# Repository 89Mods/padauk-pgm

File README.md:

# PMS150 programmer

Open-source programmer for the Padauk PMS150 / PMC150 devices, specifically the SOT23-5 variants (SOIC-8 not supported right now).

This programmer was designed to replicate the scope traces from reverse engineering of the official programmer as closely as possible. The only thing it can’t do is modulate the VDD voltage on the target device, but can change the VPP voltage to any level between 7V and 13V or shut it off entirely.

This project is not yet the simplest possible programmer, just a jumping off point for me to start optimizing from. Its actually quite overkill, as experimenting with the hardware already shows that a constant VPP of 11V is fine and, except for Q3, the FETs could be replaced by direct connections to GPIO pins on the CH32V003. The currents involved are way too tiny to require FETs to switch them. At some point in the future, I will make a new revision of this programmer that is truly as minimal as possible.

Included in this repo is also a primitive Verilog model of this MCU, together with a verilator testbench to help me test my code before I burn it onto a OTP device.

I also added support for PDK13 devices to my fork of the AS Assembler. [Check it out here.](https://github.com/AvalonSemiconductors/asl-avalonsemi/tree/avalonsemi)

The SPI programming interface does not reset properly unless ALL chip pins are floated! I believed that having the SPI lines and GND pin connected to ground while power is reset would be alright, but this breaks things. All must be floated.

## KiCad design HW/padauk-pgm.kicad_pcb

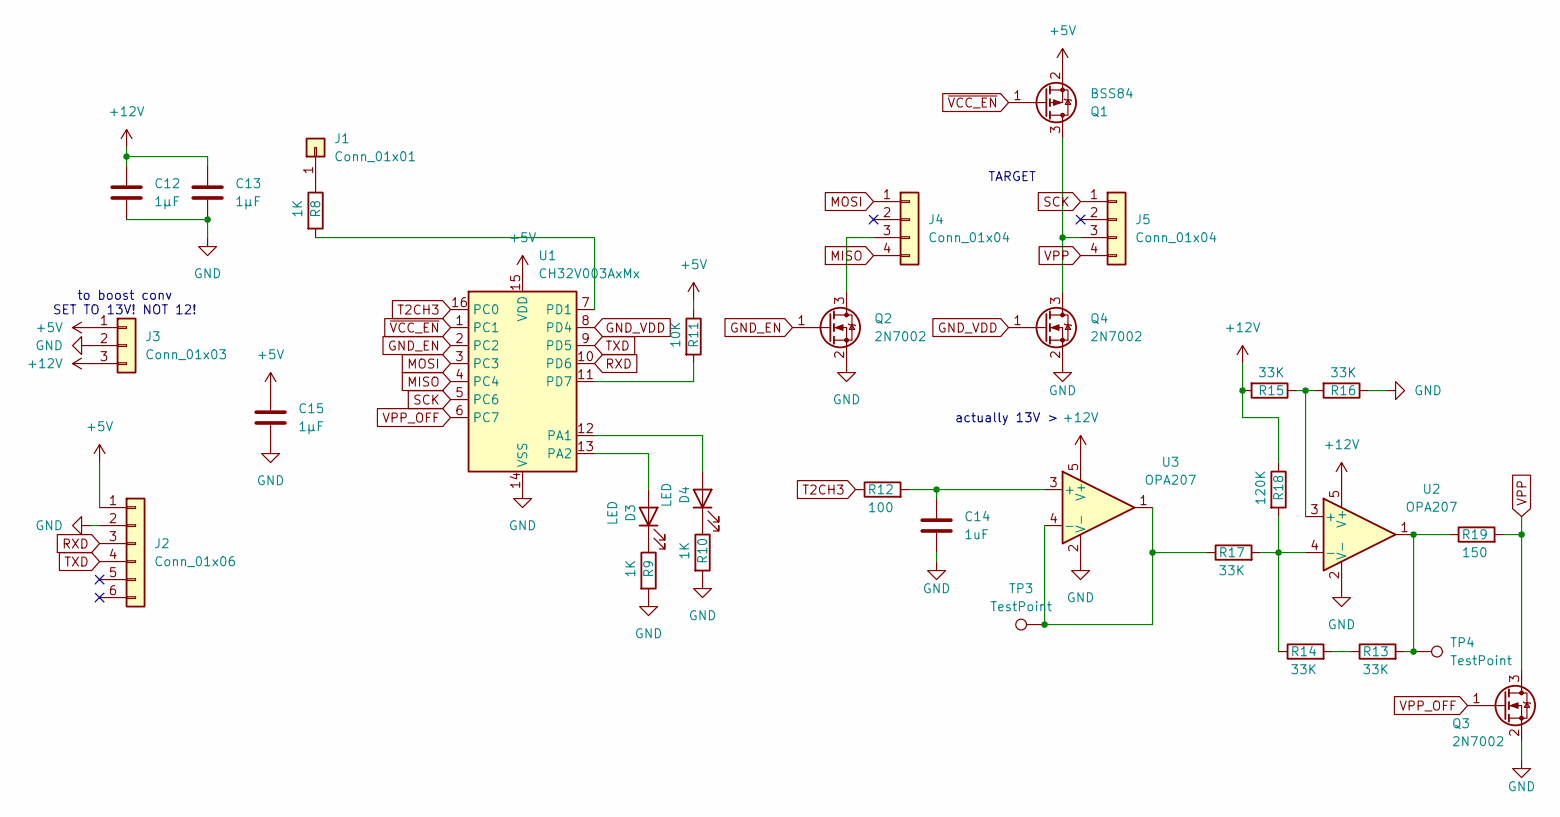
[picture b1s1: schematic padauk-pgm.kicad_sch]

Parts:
C12, C13, C15: 1µF; C_0805_2012Metric_Pad1.18x1.45mm_HandSolder
C14: 1uF; C_1206_3216Metric
D3, D4: LED; LED_1206_3216Metric_Pad1.42x1.75mm_HandSolder
J1: Conn_01x01; PinHeader_1x01_P2.54mm_Vertical
J2: Conn_01x06; PinSocket_1x06_P2.54mm_Vertical
J3: Conn_01x03; PinHeader_1x03_P2.54mm_Vertical
J4, J5: Conn_01x04; PinHeader_1x04_P2.54mm_Vertical
Q1: BSS84; SOT-23
Q2, Q3, Q4: 2N7002; SOT-23
R8, R9, R10: 1K; R_1206_3216Metric_Pad1.30x1.75mm_HandSolder
R11: 10K; R_1206_3216Metric_Pad1.30x1.75mm_HandSolder
R12: 100; R_1206_3216Metric_Pad1.30x1.75mm_HandSolder
R13, R14, R15, R16, R17: 33K; R_1206_3216Metric_Pad1.30x1.75mm_HandSolder
R18: 120K; R_1206_3216Metric_Pad1.30x1.75mm_HandSolder
R19: 150; R_1206_3216Metric_Pad1.30x1.75mm_HandSolder
TP3, TP4: TestPoint; TestPoint_Keystone_5019_Miniature
U1: CH32V003AxMx; SOP-16_3.9x9.9mm_P1.27mm
U2, U3: OPA207; SOT-23-5_HandSoldering

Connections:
+5V: C15.2, J2.1, J3.1, Q1.2 (S), R11.1, U1.15 (VDD)
+12V: C12.2, C13.2, J3.3, R15.2, R18.1, U2.5 (V+), U3.5 (V+)
GND: C12.1, C13.1, C14.1, C15.1, J2.2, J3.2, Q2.2 (S), Q3.2 (S), Q4.2 (S), R9.2, R10.2, R16.1, U1.14 (VSS), U2.2 (V-), U3.2 (V-)
GND_EN: Q2.1 (G), U1.2 (PC2)
GND_VDD: Q4.1 (G), U1.8 (PD4)
MISO: J4.4, U1.4 (PC4)
MOSI: J4.1, U1.3 (PC3)
unnamed: D3.2 (A), U1.13 (PA2)
unnamed: D3.1 (K), R9.1
unnamed: D4.2 (A), U1.12 (PA1)
unnamed: D4.1 (K), R10.1
unnamed: J1.1, R8.1
unnamed: J4.3, Q2.3 (D)
unnamed: J5.3, Q1.3 (D), Q4.3 (D)
unnamed: R13.1, R14.2
unnamed: R13.2, R19.1, TP4.1, U2.1
unnamed: R8.2, U1.7 (PD1)
unnamed: R11.2, U1.11 (PD7)
unnamed: R15.1, R16.2, U2.3 (+)
unnamed: R14.1, R17.2, R18.2, U2.4 (-)
unnamed: C14.2, R12.2, U3.3 (+)
unnamed: R17.1, TP3.1, U3.1, U3.4 (-)
RXD: J2.3, U1.10 (PD6)
SCK: J5.1, U1.5 (PC6)
T2CH3: R12.1, U1.16 (PC0)
TXD: J2.4, U1.9 (PD5)
VPP: J5.4, Q3.3 (D), R19.2
VPP_OFF: Q3.1 (G), U1.6 (PC7)
~VCC_EN: Q1.1 (G), U1.1 (PC1)

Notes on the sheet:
TARGET
to boost conv SET TO 13V! NOT 12!
actually 13V >

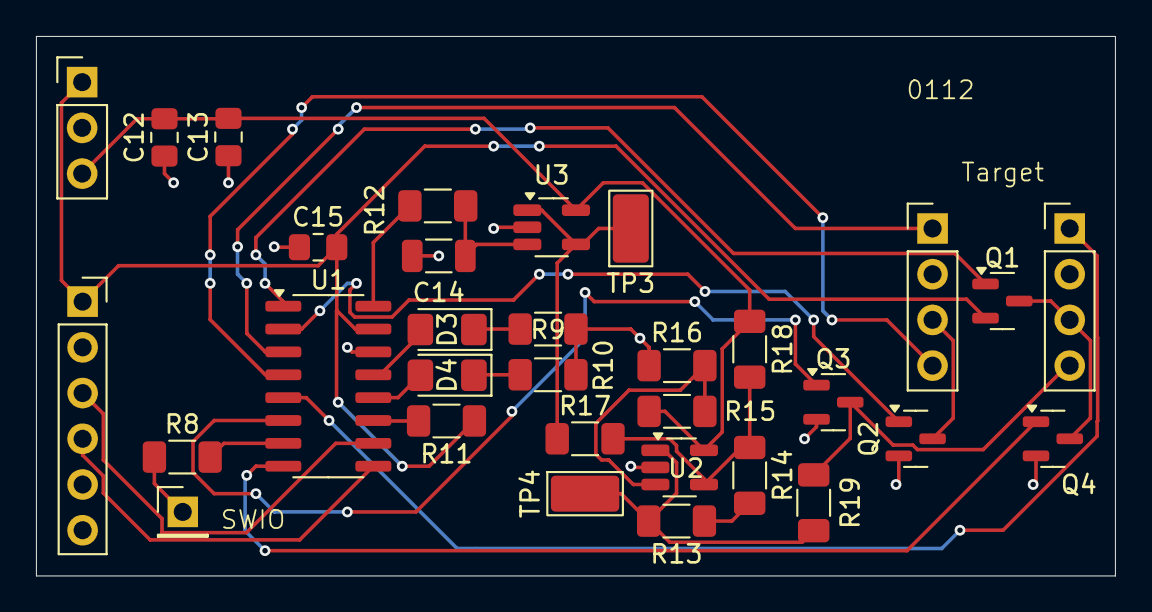
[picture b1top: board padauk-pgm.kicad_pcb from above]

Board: 2 copper layers, 59.9 x 30.0 mm, 32 parts (0 on the bottom side), 29 nets.

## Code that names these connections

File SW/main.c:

#include "funconfig.h"

#include <stdint.h>

#include "ch32fun.h"
#include "ch32v003_uart.h"

#include <stdio.h>

#define VCC_ENb PC1
#define GND_EN PC2
#define MOSI PC3
#define MISO PC4
#define SCK PC6
#define VPP_OFF PC7
#define GND_VDD PD4

#define LEVEL_10_8V 0x7E
#define LEVEL_7_5V 0xD4
#define LEVEL_LOWEST 0xFF

const char hexchars[] = "0123456789ABCDEF";

void newl() {
	UART_putc(13);
	UART_putc(10);
}

void puthex8(uint8_t c) {
	UART_putc(hexchars[c >> 4]);
	UART_putc(hexchars[c & 0xf]);
}

void puthex16(uint16_t c) {
	UART_putc(hexchars[c >> 12]);
	UART_putc(hexchars[(c >> 8) & 0xF]);
	UART_putc(hexchars[(c >> 4) & 0xF]);
	UART_putc(hexchars[c & 0xf]);
}

void puthex12(uint16_t c) {
	UART_putc(hexchars[(c >> 8) & 0xF]);
	UART_putc(hexchars[(c >> 4) & 0xF]);
	UART_putc(hexchars[c & 0xf]);
}

void power_target_on() {
	funDigitalWrite(PA1, FUN_HIGH);
	funDigitalWrite(GND_VDD, FUN_LOW);
	funDigitalWrite(VCC_ENb, FUN_LOW);
	funDigitalWrite(GND_EN, FUN_HIGH);
	funPinMode(MOSI, GPIO_Speed_10MHz | GPIO_CNF_OUT_PP);
	funPinMode(SCK, GPIO_Speed_10MHz | GPIO_CNF_OUT_PP);
	funDigitalWrite(MOSI, FUN_LOW);
	funDigitalWrite(SCK, FUN_LOW);
}

void float_target_power() {
	funDigitalWrite(GND_VDD, FUN_LOW);
	funDigitalWrite(VCC_ENb, FUN_HIGH);
	funPinMode(MOSI, GPIO_CFGLR_IN_FLOAT);
	funPinMode(SCK, GPIO_CFGLR_IN_FLOAT);
	funDigitalWrite(GND_EN, FUN_LOW);
	funPinMode(MOSI, GPIO_Speed_10MHz | GPIO_CNF_OUT_PP);
	funDigitalWrite(MOSI, FUN_LOW);
	funPinMode(SCK, GPIO_Speed_10MHz | GPIO_CNF_OUT_PP);
	funDigitalWrite(SCK, FUN_LOW);
	Delay_Us(3);
}

void power_target_off() {
	funDigitalWrite(PA1, FUN_LOW);
	TIM2->CH3CVR = LEVEL_LOWEST;
	funDigitalWrite(VPP_OFF, FUN_HIGH);
	Delay_Us(2);
	funDigitalWrite(VCC_ENb, FUN_HIGH);
	funDigitalWrite(GND_EN, FUN_HIGH);
	funDigitalWrite(GND_VDD, FUN_HIGH);
	funDigitalWrite(MOSI, FUN_LOW);
	funDigitalWrite(SCK, FUN_LOW);
	funPinMode(MOSI, GPIO_CFGLR_IN_FLOAT);
	funPinMode(SCK, GPIO_CFGLR_IN_FLOAT);
	Delay_Ms(1);
}

#define SPI_DEL 5

uint8_t spi_tfr(uint8_t val) {
	uint8_t res = 0;
	for(uint8_t i = 0; i < 8; i++) {
		if((val & 128) != 0) {funDigitalWrite(MOSI, FUN_HIGH);}
		else {funDigitalWrite(MOSI, FUN_LOW);}
		Delay_Us(SPI_DEL);
		val <<= 1;
		res <<= 1;
		if(funDigitalRead(MISO)) res |= 1;
		funDigitalWrite(SCK, FUN_HIGH);
		Delay_Us(SPI_DEL);
		funDigitalWrite(SCK, FUN_LOW);
		Delay_Us(SPI_DEL);
	}
	Delay_Us(SPI_DEL);
	return res;
}

uint16_t spi_tx13(uint16_t val) {
	uint16_t res = 0;
	for(uint8_t i = 0; i < 13; i++) {
		if((val & 4096) != 0) {funDigitalWrite(MOSI, FUN_HIGH);}
		else {funDigitalWrite(MOSI, FUN_LOW);}
		res <<= 1;
		val <<= 1;
		Delay_Us(SPI_DEL);
		if(funDigitalRead(MISO)) res |= 1;
		funDigitalWrite(SCK, FUN_HIGH);
		Delay_Us(SPI_DEL);
		funDigitalWrite(SCK, FUN_LOW);
		Delay_Us(SPI_DEL);
	}
	Delay_Us(SPI_DEL);
	return res;
}

uint16_t spi_tx12(uint16_t val) {
	uint16_t res = 0;
	for(uint8_t i = 0; i < 12; i++) {
		if((val & 2048) != 0) {funDigitalWrite(MOSI, FUN_HIGH);}
		else {funDigitalWrite(MOSI, FUN_LOW);}
		val <<= 1;
		res <<= 1;
		Delay_Us(SPI_DEL);
		if(funDigitalRead(MISO)) res |= 1;
		funDigitalWrite(SCK, FUN_HIGH);
		Delay_Us(SPI_DEL);
		funDigitalWrite(SCK, FUN_LOW);
		Delay_Us(SPI_DEL);
	}
	Delay_Us(SPI_DEL);
	return res;
}

void key_sequence(uint8_t write) {
	TIM2->CH3CVR = LEVEL_7_5V;
	float_target_power();
	funDigitalWrite(VPP_OFF, FUN_LOW);
	Delay_Us(100);
	power_target_on();
	Delay_Us(500);
	spi_tfr(0xA5); spi_tfr(0xA5); spi_tfr(0xA5); Delay_Us(1);
	spi_tfr(write ? 0xA7 : 0xA6);
	Delay_Us(10);
	if(write) {
		TIM2->CH3CVR = LEVEL_10_8V;
		Delay_Ms(15);
	}
}

uint8_t check_id(void) {
	key_sequence(1);
	spi_tx13(0x0000); spi_tx13(0x0000);
	uint16_t device_id = 0;
	device_id = spi_tx12(0x000);
	power_target_off();
	Delay_Ms(50);
	if(device_id != 0xA16) {
		UART_printf("Invalid device ID %x\r\n", device_id);
		return 1;
	}
	return 0;
}

uint8_t UART_waitForChar(void) {
	uint16_t i;
	while(1) {
		i = UART_getc();
		if(i == UART_NO_DATA) continue;
		if((i & 0xFF00) != 0) return 0;
		return i & 0xFF;
	}
}

#define CHIP_SIZE 1024
#define CHIP_SIZE_PROGRAMMABLE (1024-16)

uint8_t doDump(void) {
	if(check_id()) return 1;
	key_sequence(0);
	for(uint16_t i = 0; i < CHIP_SIZE; i++) {
		spi_tx12(i);
		funDigitalWrite(SCK, FUN_HIGH);
		uint16_t val = spi_tx13(0);
		if((i & 15) == 0) {
			UART_putc(13);
			UART_putc(10);
			puthex12(i);
		}
		UART_putc(' ');
		puthex16(val);
	}
	UART_putc(13);
	UART_putc(10);
	power_target_off();
	Delay_Ms(50);
	return 0;
}

uint8_t doProgramming(void) {
	if(check_id()) return 2;
	key_sequence(0);
	for(uint16_t i = 0; i < CHIP_SIZE_PROGRAMMABLE; i++) {
		spi_tx12(i);
		funDigitalWrite(SCK, FUN_HIGH);
		uint16_t val = spi_tx13(0);
		if(val != 0x1FFF) {
			power_target_off();
			Delay_Ms(50);
			UART_printf("Chip not blank, programmed word found at address 0x%x\r\n", i);
			return 1;
		}
	}
	power_target_off();
	Delay_Ms(50);
	UART_putc('a');
	uint32_t len = UART_waitForChar() - 'A';
	len |= (uint16_t)(UART_waitForChar() - 'A') << 4;
	len |= (uint16_t)(UART_waitForChar() - 'A') << 8;
	len |= (uint16_t)(UART_waitForChar() - 'A') << 12;
	if(len > CHIP_SIZE_PROGRAMMABLE) {
		UART_printf("THAT’S TOO BIG!\r\n");
		return 1;
	}
	if((len & 1) != 0) {
		UART_printf("Uneven size not permitted\r\n");
		return 1;
	}
	uint8_t uneven = len & 3;
	uint32_t end = len >> 2;
	if(uneven) end++;
	key_sequence(1);
	for(uint32_t i = 0; i < end; i++) {
		UART_putc('n');
		uint16_t val = UART_waitForChar();
		UART_putc('n');
		val |= (uint16_t)UART_waitForChar() << 8;
		uint16_t val2 = 0x1FFF;
		if(!(i == end - 1 && uneven)) {
			UART_putc('n');
			val2 = UART_waitForChar();
			UART_putc('n');
			val2 |= (uint16_t)UART_waitForChar() << 8;
		}
		spi_tx13(val);
		spi_tx13(val2);
		spi_tx12(i << 1);
		//Send 0 bit to initiate write
		funDigitalWrite(MOSI, FUN_LOW);
		Delay_Us(SPI_DEL);
		funDigitalWrite(SCK, FUN_HIGH);
		Delay_Us(SPI_DEL);
		funDigitalWrite(SCK, FUN_LOW);
		Delay_Us(SPI_DEL);
		funDigitalWrite(SCK, FUN_HIGH);
		Delay_Us(SPI_DEL * 2);
		for(uint8_t j = 0; j < 8; j++) {
			funDigitalWrite(MOSI, FUN_HIGH);
			Delay_Us(61);
			funDigitalWrite(MOSI, FUN_LOW);
			Delay_Us(61);
		}
		Delay_Us(SPI_DEL);
		funDigitalWrite(SCK, FUN_LOW);
		//Trailing 0 bit to end write
		Delay_Us(SPI_DEL);
		funDigitalWrite(SCK, FUN_HIGH);
		Delay_Us(SPI_DEL);
		funDigitalWrite(SCK, FUN_LOW);
		Delay_Us(SPI_DEL);
	}
	power_target_off();
	UART_putc('d');
	key_sequence(0);
	for(uint32_t i = 0; i < end; i++) {
		UART_waitForChar();
		spi_tx12(i << 1);
		funDigitalWrite(SCK, FUN_HIGH);
		uint16_t val = spi_tx13(0);
		UART_putc((val & 15) + 48);
		UART_putc(((val >> 4) & 15) + 48);
		UART_waitForChar();
		val >>= 8;
		UART_putc((val & 15) + 48);
		UART_putc(((val >> 4) & 15) + 48);
		if(!(i == end - 1 && uneven)) {
			UART_waitForChar();
			spi_tx12((i << 1) | 1);
			funDigitalWrite(SCK, FUN_HIGH);
			val = spi_tx13(0);
			UART_putc((val & 15) + 48);
			UART_putc(((val >> 4) & 15) + 48);
			UART_waitForChar();
			val >>= 8;
			UART_putc((val & 15) + 48);
			UART_putc(((val >> 4) & 15) + 48);
		}
	}
	power_target_off();
	return 0;
}

int main() {
	SystemInit();
	AFIO->PCFR1 &= ~(1 << 15);
	RCC->CTLR &= ~(1 << 16);
	funGpioInitAll();
	UART_init();
	funPinMode( PC0,     GPIO_Speed_10MHz | GPIO_CNF_OUT_PP_AF );
	funPinMode( PD5,     GPIO_Speed_10MHz | GPIO_CNF_OUT_PP_AF );
	
	RCC->APB1PCENR |= RCC_APB1Periph_TIM2;
	RCC->APB1PRSTR |= RCC_APB1Periph_TIM2;
	RCC->APB1PRSTR &= ~RCC_APB1Periph_TIM2;
	TIM2->PSC = 0x0000;
	TIM2->ATRLR = 255;
	TIM2->CHCTLR2 |= TIM_OC3M_2 | TIM_OC3M_1 | TIM_OC3PE;
	TIM2->CTLR1 |= TIM_ARPE;
	TIM2->CCER |= TIM_CC3E | (TIM_CC3P & 0xff);
	TIM2->SWEVGR |= TIM_UG;
	TIM2->CTLR1 |= TIM_CEN;
	TIM2->CH3CVR = LEVEL_LOWEST;
	
	funPinMode(VCC_ENb, GPIO_Speed_10MHz | GPIO_CNF_OUT_PP);
	funDigitalWrite(VCC_ENb, FUN_HIGH);
	funPinMode(GND_EN, GPIO_Speed_10MHz | GPIO_CNF_OUT_PP);
	funDigitalWrite(GND_EN, FUN_HIGH);
	funPinMode(MOSI, GPIO_CFGLR_IN_FLOAT);
	funPinMode(SCK, GPIO_CFGLR_IN_FLOAT);
	
	funPinMode(MISO, GPIO_CFGLR_IN_PUPD);
	funPinMode(VPP_OFF, GPIO_Speed_10MHz | GPIO_CNF_OUT_PP);
	funDigitalWrite(VPP_OFF, FUN_HIGH);
	funPinMode(GND_VDD, GPIO_Speed_10MHz | GPIO_CNF_OUT_PP);
	funDigitalWrite(GND_VDD, FUN_HIGH);
	
	funPinMode(PA2, GPIO_Speed_10MHz | GPIO_CNF_OUT_PP);
	funDigitalWrite(PA2, FUN_HIGH);
	funPinMode(PA1, GPIO_Speed_10MHz | GPIO_CNF_OUT_PP);
	funDigitalWrite(PA1, FUN_LOW);
	
	while(1) {
		power_target_off();
		UART_printf("\r\nPress 9 to continue\r\n");
		Delay_Ms(50);
		uint8_t mode = 0;
		while(1) {
			mode = UART_getc();
			if(mode == '9') break;
			Delay_Ms(1);
		}
		UART_printf("Press r to dump ROM\r\n");
		while(1) {
			mode = UART_getc();
			if(mode == 'r') {
				doDump();
				break;
			}
			if(mode == 'p') {
				doProgramming();
				break;
			}
			Delay_Ms(1);
		}
		
		Delay_Ms(509);
	}
}

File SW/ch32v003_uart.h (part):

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 * 
 *	USART1 mapping configuration high (used in conjunction with AFIO PCFR1 register bit2
 *	USART1RM [21,2]).
 * 	00: default mapping (CK/PD4, TX/PD5, RX/PD6, CTS/PD3, RTS/PC2, SW_RX/PD5).
 *	01: Remapping (CK/PD7, TX/PD0, RX/PD1, CTS/PC3, RTS/PC2, SW_RX/PD0).
 *	10: Remapping (CK/PD7, TX/PD6, RX/PD5, CTS/PC6, RTS/PC7, SW_RX/PD6).
 *	11: Remapping (CK/PC5, TX/PC0, RX/PC1, CTS/PC6, RTS/PC7, SW_RX/PC0).
 *
 * Usage:
 * 1. In funconfig.h define the baudrate:
 *    #define FUNCONF_UART_PRINTF_BAUD 115200 //used for uart library
 * 
 * 2. In main source file: optionally define the TXRX pin configuration. If not defined
 *    the standard TX=PD5, RX=PD6 is used, alternative settings:
 *    #define UART_PINS_TXPD0_RXPD1 or
 *    #define UART_PINS_TXPC0_RXPC1 or
 *    #define UART_PINS_TXPD6_RXPD5 - this is the TXRX swap setting
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
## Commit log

2025-06-11 Initial commit.
2025-06-20 Verilog bench fixes
